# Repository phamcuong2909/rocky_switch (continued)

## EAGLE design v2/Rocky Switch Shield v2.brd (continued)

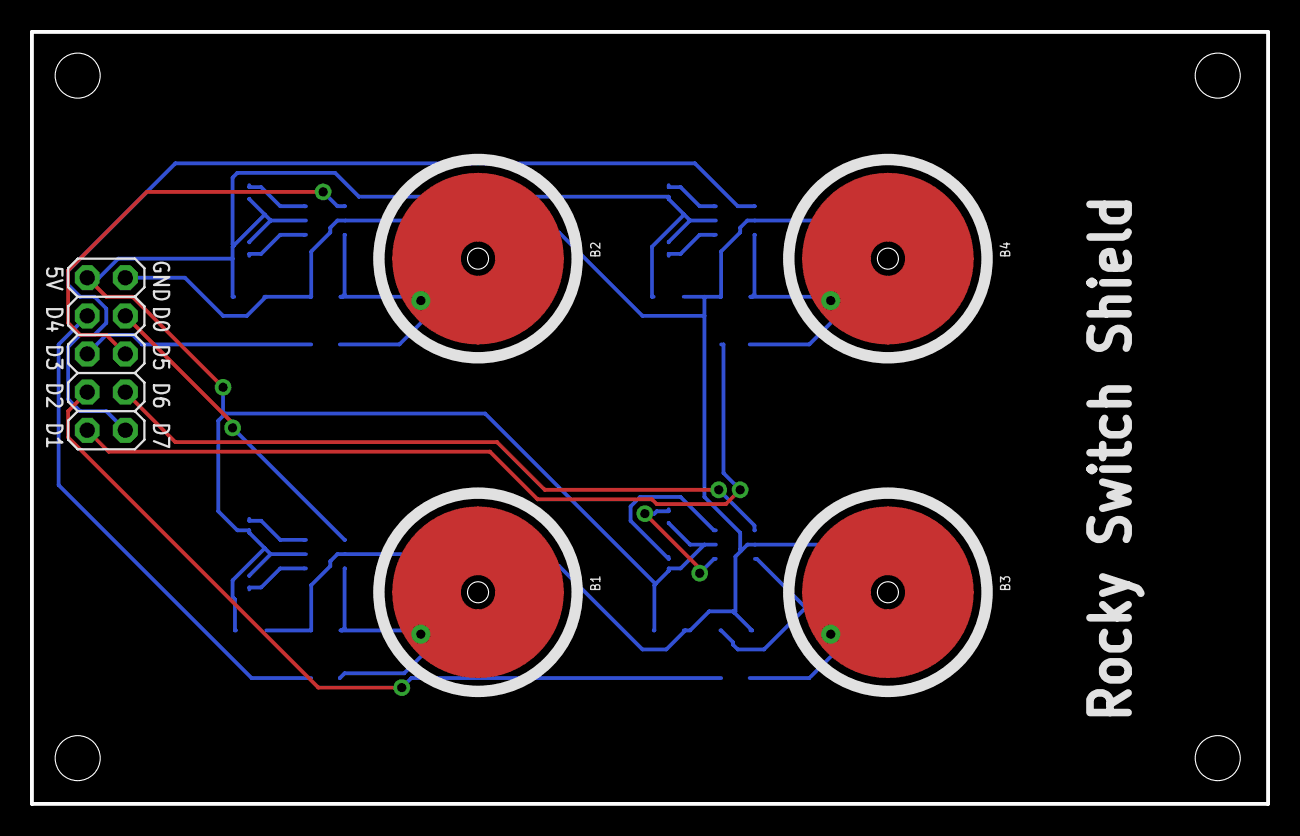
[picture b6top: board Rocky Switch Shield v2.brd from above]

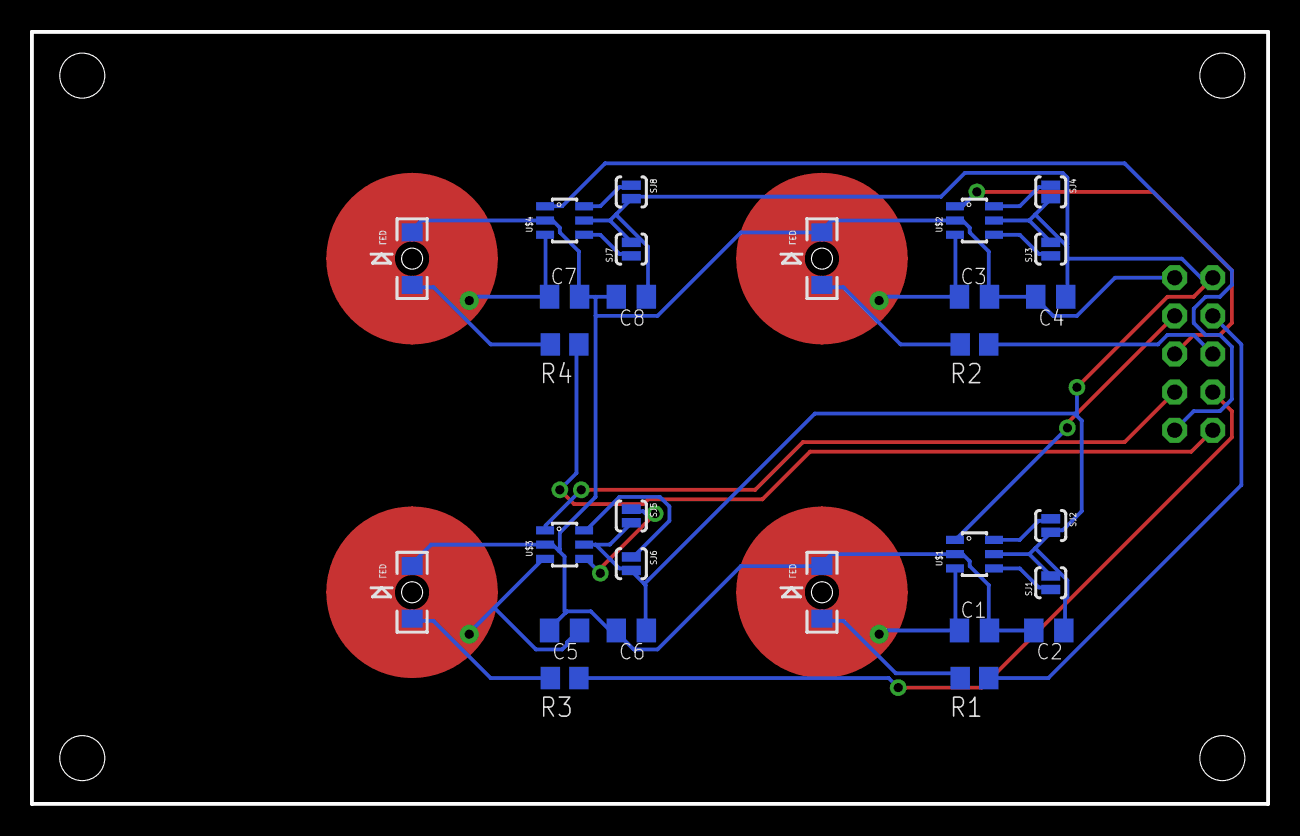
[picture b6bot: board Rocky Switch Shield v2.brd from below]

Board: 2 copper layers, 82.3 x 51.4 mm, 33 parts (24 on the bottom side), 26 nets.

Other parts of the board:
U$6, U$7, U$8, U$9: KFH-M3

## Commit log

2016-07-04 Add sample code and schematics
2016-07-15 Add new version of switchboard using ssr
2016-08-08 Update the code to handle button debounce better
2016-08-09 Update to new version to back to use SSR instead of mechanical relays
2016-08-09 Remove unused design files
2016-08-25 Update new shield for rocky switch
2016-11-09 Update sample code
2016-11-27 Add new sample code to control switch via web
2017-01-05 Sample code for aQuoc
2017-02-19 Correct shield
2017-06-09 Add new rocky using relays
2017-06-09 Add shield for rocky relay
2017-06-11 Update shield relay to move touch ICs to the left
